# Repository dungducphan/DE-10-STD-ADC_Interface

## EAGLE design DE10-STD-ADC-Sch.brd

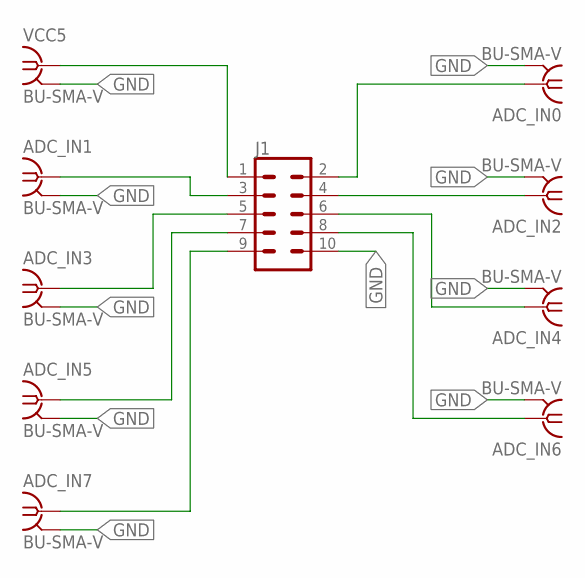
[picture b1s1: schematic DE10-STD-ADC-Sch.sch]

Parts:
ADC_IN0, ADC_IN1, ADC_IN2, ADC_IN3, ADC_IN4, ADC_IN5, ADC_IN6, ADC_IN7: BU-SMA-V
J1: CONN_05X2SHD-NS; 2X5-SHROUDED-NS
VCC5: BU-SMA-V

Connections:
GND: ADC_IN0.2, ADC_IN0.3 (2), ADC_IN0.4 (2), ADC_IN0.5 (2), ADC_IN1.2, ADC_IN1.3 (2), ADC_IN1.4 (2), ADC_IN1.5 (2), ADC_IN2.2, ADC_IN2.3 (2), ADC_IN2.4 (2), ADC_IN2.5 (2), ADC_IN3.2, ADC_IN3.3 (2), ADC_IN3.4 (2), ADC_IN3.5 (2), ADC_IN4.2, ADC_IN4.3 (2), ADC_IN4.4 (2), ADC_IN4.5 (2), ADC_IN5.2, ADC_IN5.3 (2), ADC_IN5.4 (2), ADC_IN5.5 (2), ADC_IN6.2, ADC_IN6.3 (2), ADC_IN6.4 (2), ADC_IN6.5 (2), ADC_IN7.2, ADC_IN7.3 (2), ADC_IN7.4 (2), ADC_IN7.5 (2), J1.10, VCC5.2, VCC5.3 (2), VCC5.4 (2), VCC5.5 (2)
unnamed: J1.1, VCC5.1
unnamed: ADC_IN1.1, J1.3
unnamed: ADC_IN3.1, J1.5
unnamed: ADC_IN5.1, J1.7
unnamed: ADC_IN7.1, J1.9
unnamed: ADC_IN0.1, J1.2
unnamed: ADC_IN2.1, J1.4
unnamed: ADC_IN4.1, J1.6
unnamed: ADC_IN6.1, J1.8

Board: 2 copper layers, 10 parts (0 on the bottom side), 10 nets, no tracks yet.

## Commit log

2019-03-09 First commit.

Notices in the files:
parts and their libraries:
SparkFun-Connectors: Licensing: Creative Commons ShareAlike 4.0 International - https://creativecommons.org/licenses/by-sa/4.0
